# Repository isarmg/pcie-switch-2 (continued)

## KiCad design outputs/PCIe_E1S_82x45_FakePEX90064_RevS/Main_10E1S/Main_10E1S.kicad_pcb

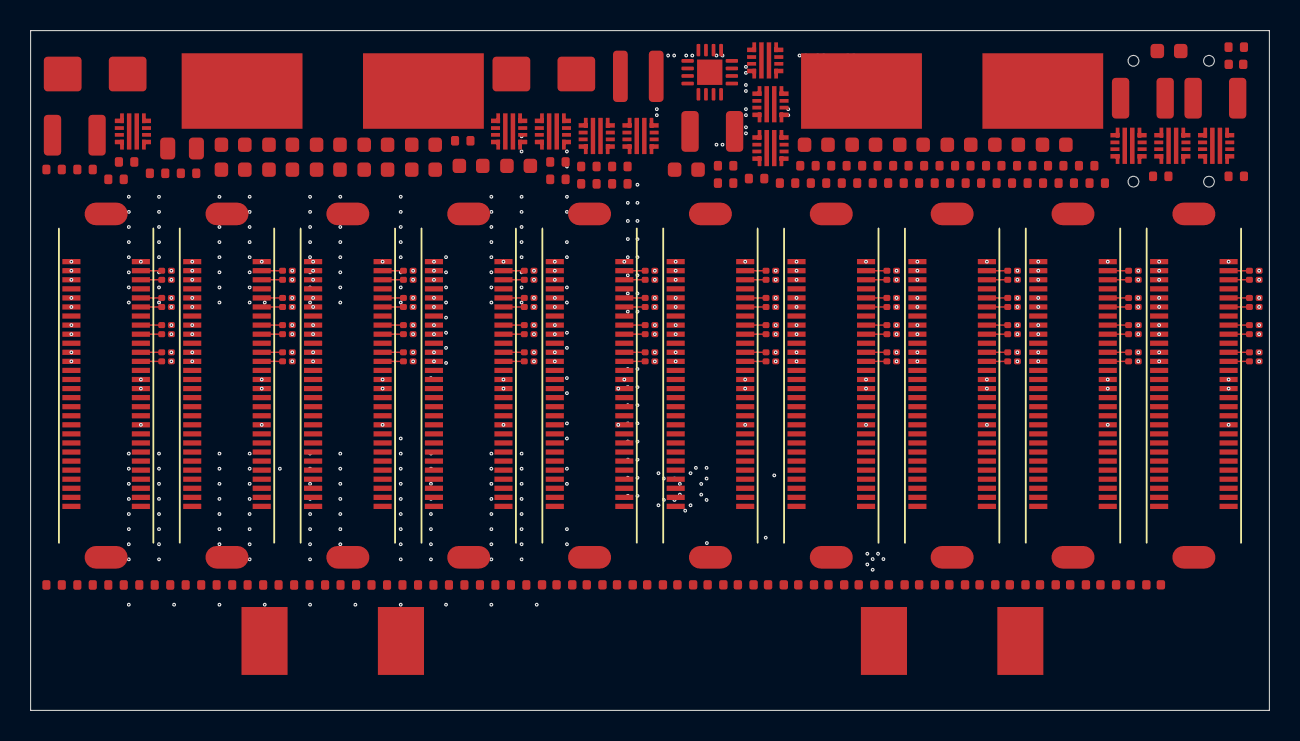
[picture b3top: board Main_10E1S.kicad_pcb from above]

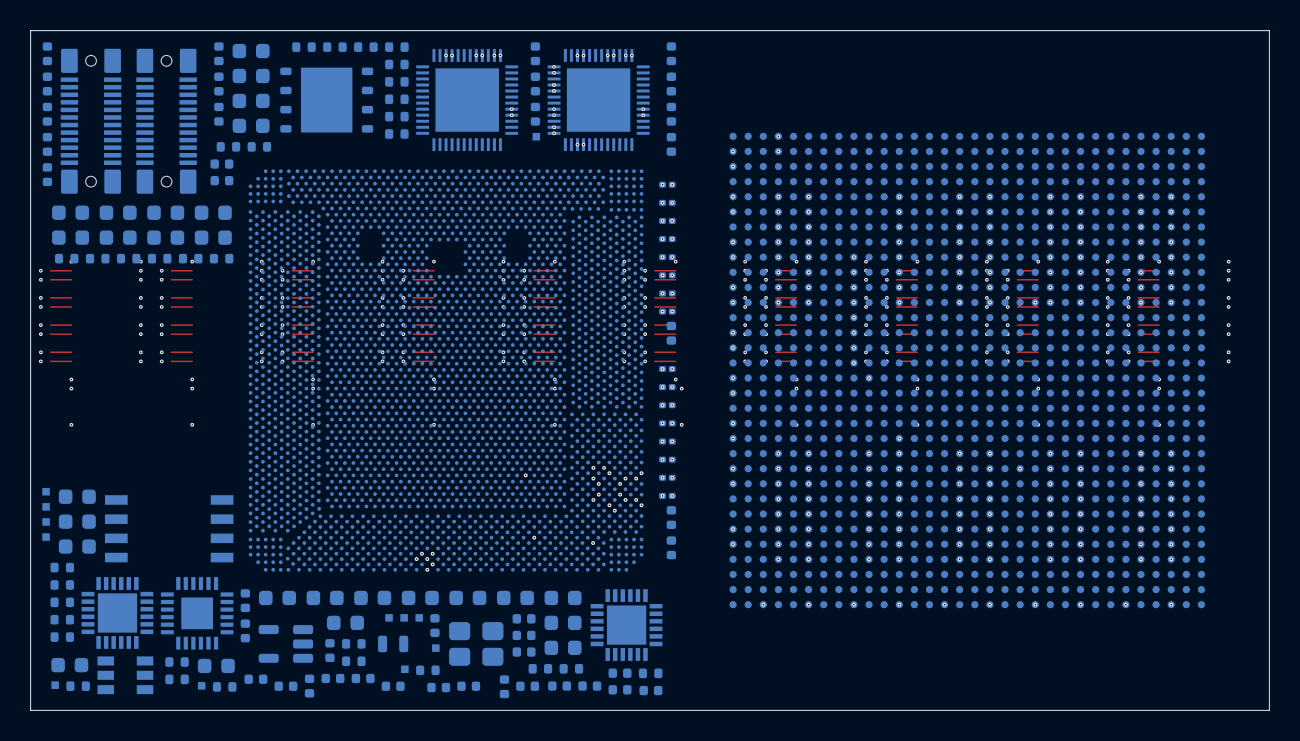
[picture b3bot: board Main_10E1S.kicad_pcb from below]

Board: 32 copper layers, 82.0 x 45.0 mm, 357 parts (145 on the bottom side), 466 nets.

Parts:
C1, C2: 10uF 25V X7R; C_1210_3225Metric
C101, C104, C107, C110, C113, C116, C119, C122, C125, C128, C301: 10nF 25V; C_0402_1005Metric
C102, C105, C108, C111, C114, C117, C120, C123, C126, C129: 100nF 50V; C_0603_1608Metric
C103, C106, C109, C112, C115, C118, C121, C124, C127, C130: 1uF 25V; C_0603_1608Metric
C311: 10uF 25V; C_0805_2012Metric
C312: 100nF 50V; C_0402_1005Metric
C313: 3.3nF 25V; C_0402_1005Metric
C314, C315: 47uF 16V; C_1210_3225Metric
C701, C720, C721, C722, C723, C724, C725, C726, C727, C728, C730, C731, C732, C733, C734, C735, C736, C737, C738, C742: 100nF; C_0402_1005Metric
C702, C707, C708: 1uF; C_0402_1005Metric
C703, C704: 18pF DNP TUNE; C_0402_1005Metric
C705, C706: 8.2pF DNP TUNE; C_0402_1005Metric
C709, C710: 100nF RC reset draft; C_0402_1005Metric
C741: 47nF / reset delay; C_0402_1005Metric
C801, C802, C803, C804, C805, C806, C807, C808, C811, C812, C813, C814, C815, C816, C817, C818: 220nF 16V / GRM033R61C224KE14D; C_0201_0603Metric
C901, C903, C905, C907, C909, C911, C913, C915, C917, C919, C921, C923, C925, C927, C929, C931, C933: 100nF / PDN budget; C_0402_1005Metric
C902, C904, C906, C908, C910, C912, C914, C916, C918, C920, C922, C924, C926, C928, C930, C932, C934: 4.7uF / PDN budget; C_0603_1608Metric
C951, C952, C953, C954, C955, C956, C957, C958, C959, C960: 4.7uF / EDGECAP value pending PDG; C_0603_1608Metric
C965, C966, C967, C968: 1uF / filter value pending PDG; C_0402_1005Metric
C4001, C4002, C4003, C4004, C4005, C4006, C4007, C4008, C4009, C4010, C4011, C4012, C4013, C4014, C4015, C4016, C4017, C4018, C4019, C4020, C4021, C4022, C4023, C4024, C4025, C4026, C4027, C4028, C4029, C4030, C4031, C4032, C4033, C4034, C4035, C4036, C4037, C4038, C4039, C4040, C4041, C4042, C4043, C4044, C4045, C4046, C4047, C4048, C4049, C4050, C4051, C4052, C4053, C4054, C4055, C4056, C4057, C4058, C4059, C4060, C4061, C4062, C4063, C4064, C4065, C4066, C4067, C4068, C4069, C4070, C4071, C4072, C4073, C4074, C4075, C4076, C4077, C4078, C4079, C4080: 220nF 16V / GRM033R61C224KE14D; C_0201_0603Metric_DenseCourtyard_1p30x0p55
D1, D2: SMBJ13CA; D_SMB
F1, F2: 20A 125V; Littelfuse_456_20A
J1, J2, J3, J4, J5, J6, J7, J8, J9, J10: HSEC6-028-01-S-DV-WT-TR; Samtec_HSEC6-028-01-S-DV-WT
J11: 12V 15A FEED A; WireSolder_2x_8x5_P12
J12: 12V 15A FEED B; WireSolder_2x_8x5_P12
J401: CUSTOM 12V POWER / SMT SHELL DRAFT; USB_C_24P_Vertical_SMT_Shell_7p46_CUSTOM_DRAFT
J402: TB5 PORT / SMT SHELL DRAFT / PART TBD; USB_C_24P_Vertical_SMT_Shell_7p46_CUSTOM_DRAFT
L31: 2.2uH; L_Coilcraft_XAL4020-XXX
R101, R106, R111, R116, R121, R126, R131, R136, R141, R146, R301: 76.1k; R_0402_1005Metric
R102, R104, R107, R109, R112, R114, R117, R119, R122, R124, R127, R129, R132, R134, R137, R139, R142, R144, R147, R149, R302, R304, R702, R703, R704, R712, R713, R724, R725: 10k; R_0402_1005Metric
R103, R108, R113, R118, R123, R128, R133, R138, R143, R148, R303: 102k; R_0402_1005Metric
R105, R110, R115, R120, R125, R130, R135, R140, R145, R150: 1.10k; R_0402_1005Metric
R305: 3.32k; R_0402_1005Metric
R311, R401, R402, R710, R711: 100k; R_0402_1005Metric
R701: 22R provisional SI tuning; R_0402_1005Metric
R705: 180R 1% / Intel clock topology; R_0402_1005Metric
R706, R707: TBD RCOMP / DNP / Intel PDG required; R_0402_1005Metric
R708, R709: 200R 1%; R_0402_1005Metric
R714, R715, R716: 0R / request clock always on; R_0402_1005Metric
R721, R722: 0R analog supply link / filter pending; R_0402_1005Metric
R730, R731, R732: DNP / filter link pending Intel PDG; R_0402_1005Metric
R740, R741, R742, R743, R744, R745, R746: 10k / Intel required external bias; R_0402_1005Metric
TP701: PROBE /CPU_SVID_CLK_1V25; Probe_0p5mm
TP702: PROBE /CPU_SVID_DATA_1V25; Probe_0p5mm
TP703: PROBE /CPU_SVID_ALERT_1V25_N; Probe_0p5mm
TP704: PROBE /CPU_PLT_PWROK; Probe_0p5mm
TP705: PROBE /CPU_SYS_PWROK_1V8; Probe_0p5mm
TP706: PROBE /CPU_RSMRST_N; Probe_0p5mm
TP707: PROBE /CPU_SYS_RESET_1V8_N; Probe_0p5mm
TP708: PROBE /CPU_PWRBTN_1V8_N; Probe_0p5mm
TP709: PROBE /CPU_VCCST_EN_1V8; Probe_0p5mm
TP710: PROBE /CPU_SLP_S3_1V8_N; Probe_0p5mm
TP711: PROBE /CPU_SLP_S4_1V8_N; Probe_0p5mm
TP712: PROBE /CPU_SLP_S5_1V8_N; Probe_0p5mm
U1: PEX90064 / FAKE 64-lane 33x33 BGA1024; PEX90064_FAKE_BGA1024_33x33_P1_Reordered_NOT_REAL
U11, U12, U13, U14, U15, U16, U17, U18, U19, U20, U30: TPS259470ARPWR; TI_RPW0010A_TPS25947
U31: TPS62132RGTR; VQFN-16-1EP_3x3mm_P0.5mm_EP1.68x1.68mm
U501: Intel_JHL9580_MECH_13x13_UNVERIFIED
U502: Intel Core Ultra 9 288V / 32GB LPDDR5X MoP / BGA2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; Intel_Core_Ultra_200V_BGA2833_27p5x27_ExactXY_DraftLands
U601: 9ZXL0851EKILFT / CPU common clock 100MHz; REF_9ZXL0851EKILFT_KU1
U602: 9ZXL0851EKILFT / CPU common clock 100MHz; REF_9ZXL0851EKILFT_KU3
U603: 9FGV0241AKLF / DNP ALTERNATE CLOCK; REF_9FGV0241AKLF_KU2
U604: 9DML0451AKILF / DNP ALTERNATE CLOCK; REF_9DML0451AKILF_KU5
U605: TPS3808G09DBVR / SUPPORT NETWORK PENDING; REF_TPS3808G09DBVR_FU1
U606: W25Q32JWSSIQ_C2980995 / SUPPORT NETWORK PENDING; REF_W25Q32JWSSIQ_FU2
U607: TCA9548ARGER / SUPPORT NETWORK PENDING; REF_TCA9548ARGER_SU1
U701: W25Q256JWPIQ / 1.8V 32MiB BIOS; WSON-8-1EP_6x5mm_P1.27mm_EP3.4x4.3mm
U702: TPS7A0215PDBVR / RTC 1.5V; SOT-23-5
Y701: 38.4MHz crystal / load and ESR selection pending; Crystal_SMD_3225-4Pin_3.2x2.5mm
Y702: 32.768kHz crystal / load and ESR selection pending; Crystal_SMD_2012-2Pin_2.0x1.2mm

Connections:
/AUX_12V_PROTECTED: C311.1, C312.1, U30.6, U31.10, U31.11, U31.12, U31.13
/AUX_DVDT: C301.1, U30.7
/AUX_ILM: R305.1, U30.9
/AUX_OV: R303.2, R304.1, U30.2
/AUX_PG: R311.2, U31.4
/AUX_UV: R301.2, R302.1, U30.1
/BUCK_SS: C313.1, U31.9
/BUCK_SW: L31.1, U31.1, U31.2, U31.3
/CLKBUF1_VDDA: C728.1, R721.2, U601.44
/CLKBUF2_VDDA: C738.1, R722.2, U602.44
/CPU_ACPRESENT: R741.1, U502.P45
/CPU_BATLOW_N: R740.1, U502.R50
/CPU_CLKBUF1_IN_N: U502.BC2, U601.5
/CPU_CLKBUF1_IN_P: U502.BB1, U601.4
/CPU_CLKBUF2_IN_N: U502.AY4, U602.5
/CPU_CLKBUF2_IN_P: U502.AW3, U602.4
/CPU_CLKREQ0_N: R714.1, U502.B55
/CPU_CLKREQ1_N: R715.1, U502.F50
/CPU_CLKREQ2_N: R716.1, U502.E51
/CPU_CLK_RCOMP: R705.1, U502.BG3
/CPU_EPD_ON_LOOP_1V25: U502.AB27, U502.Y27
/CPU_G5_RX0_N: C812.2, U502.DD16
/CPU_G5_RX0_P: C811.2, U502.DE14
/CPU_G5_RX1_N: C814.2, U502.DA18
/CPU_G5_RX1_P: C813.2, U502.CY17
/CPU_G5_RX2_N: C816.2, U502.CY22
/CPU_G5_RX2_P: C815.2, U502.DA21
/CPU_G5_RX3_N: C818.2, U502.DC24
/CPU_G5_RX3_P: C817.2, U502.DD23
/CPU_G5_TX0_N: C802.1, U502.DL16
/CPU_G5_TX0_P: C801.1, U502.DK17
/CPU_G5_TX1_N: C804.1, U502.DH17
/CPU_G5_TX1_P: C803.1, U502.DF18
/CPU_G5_TX2_N: C806.1, U502.DH22
/CPU_G5_TX2_P: C805.1, U502.DF21
/CPU_G5_TX3_N: C808.1, U502.DL23
/CPU_G5_TX3_P: C807.1, U502.DK22
/CPU_PCIE4_RCOMP: R706.1, U502.DL39
/CPU_PCIE5_RCOMP: R707.1, U502.DA1
/CPU_PERST_1V8_N: R725.1, U1.AM32, U502.F24, U605.3
/CPU_PEX_RX0_N: C802.2, U1.AD32
/CPU_PEX_RX0_P: C801.2, U1.AC32
/CPU_PEX_RX1_N: C804.2, U1.AA32
/CPU_PEX_RX1_P: C803.2, U1.Y32
/CPU_PEX_RX2_N: C806.2, U1.V32
/CPU_PEX_RX2_P: C805.2, U1.U32
/CPU_PEX_RX3_N: C808.2, U1.R32
/CPU_PEX_RX3_P: C807.2, U1.P32
/CPU_PEX_TX0_N: C812.1, U1.M32
/CPU_PEX_TX0_P: C811.1, U1.L32
/CPU_PEX_TX1_N: C814.1, U1.J32
/CPU_PEX_TX1_P: C813.1, U1.H32
/CPU_PEX_TX2_N: C816.1, U1.F32
/CPU_PEX_TX2_P: C815.1, U1.E32
/CPU_PEX_TX3_N: C818.1, U1.C32
/CPU_PEX_TX3_P: C817.1, U1.B32
/CPU_PLT_PWROK: R745.1, TP704.1, U502.H13
/CPU_PMCALERT_N: R742.1, U502.F42
/CPU_PWRBTN_1V8_N: R713.1, TP708.1, U502.P47
/CPU_REFCLK_N: U1.AH32, U502.BC4
/CPU_REFCLK_P: U1.AG32, U502.BB3
/CPU_RSMRST_N: R744.1, TP706.1, U502.E13
/CPU_RTCRST_N: C709.1, R710.1, U502.H15
/CPU_RTCX1: C705.1, U502.A12, Y702.1
/CPU_RTCX2: C706.1, U502.A10, Y702.2
/CPU_SLP_S3_1V8_N: TP710.1, U502.M44
/CPU_SLP_S4_1V8_N: TP711.1, U502.L55
/CPU_SLP_S5_1V8_N: TP712.1, U502.P53
/CPU_SPI_CLK_FLASH: R701.2, U701.6
/CPU_SPI_CLK_PAD: R701.1, U502.W13
/CPU_SPI_CS0_N: R702.1, U502.AC17, U701.1
/CPU_SPI_IO0: U502.AA17, U701.5
/CPU_SPI_IO1: U502.AE17, U701.2
/CPU_SPI_IO2: R703.1, U502.W17, U701.3
/CPU_SPI_IO3: R704.1, U502.U13, U701.7
/CPU_SRTCRST_N: C710.1, R711.1, U502.B15
/CPU_SVID_ALERT_1V25_N: TP703.1, U502.F56
/CPU_SVID_CLK_1V25: TP701.1, U502.E55
/CPU_SVID_DATA_1V25: TP702.1, U502.C56
/CPU_SYS_PWROK_1V8: R746.1, TP705.1, U502.H31
/CPU_SYS_RESET_1V8_N: R712.1, TP707.1, U502.M52
/CPU_USB2_RCOMP: R708.1, U502.W1
/CPU_USB32_RCOMP: R709.1, U502.BG1
/CPU_V1P8U_MEM: C901.1, C902.1, U502.AK67, U502.AK70, U502.AL69, U502.AM67, U502.AM70, U502.AP67, U502.AP70, U502.AR69, U502.AT67, U502.AT70, U502.AT73, U502.AT76, U502.AT79, U502.AU69, U502.AU75, U502.AU80, U502.AV67, U502.AV70, U502.AV73, U502.AV76, U502.AV79, U502.AW69, U502.AW72, U502.AW75, U502.AW77, U502.AW80, U502.AY67, U502.AY70, U502.AY73, U502.AY76, U502.AY79, U502.BA72, U502.BA77, U502.BB67, U502.BB70, U502.BB73, U502.BB76, U502.BB79, U502.BC69, U502.BC77, U502.BC80, U502.BD67, U502.BD79, U502.BD82, U502.BD85, U502.BD88, U502.BD90, U502.BD93, U502.BE69, U502.BE80, U502.BE86, U502.BF67, U502.BF79, U502.BF82, U502.BF85, U502.BF88, U502.BF90, U502.BF93, U502.BG69, U502.BG77, U502.BG80, U502.BG83, U502.BG86, U502.BG89, U502.BG92, U502.BH67, U502.BH79, U502.BH82, U502.BH85, U502.BH88, U502.BH90, U502.BH93, U502.BJ77, U502.BK67, U502.BK79, U502.BL69, U502.BL72, U502.BL77, U502.BL80, U502.BM67, U502.BM70, U502.BM73, U502.BM76, U502.BM79, U502.BN69, U502.BN75, U502.BN80, U502.BP67, U502.BP70, U502.BP73, U502.BP76, U502.BP79, U502.BR69, U502.BR72, U502.BR75, U502.BR77, U502.BR80, U502.BT67, U502.BT70, U502.BT73, U502.BT76, U502.BT79, U502.BV67, U502.BV70, U502.BW69, U502.BY67, U502.BY70, U502.CA69, U502.CB67, U502.CB70
/CPU_V1P8U_MEM_EDGECAP_0: C951.1, U502.B69, U502.B71
/CPU_V1P8U_MEM_EDGECAP_1: C952.1, U502.AE92, U502.AG92
/CPU_V1P8U_MEM_EDGECAP_2: C953.1, U502.CE92, U502.CG92
/CPU_V1P8U_MEM_EDGECAP_3: C954.1, U502.DK68, U502.DK70
/CPU_VCCGT: C903.1, C904.1, U502.A34, U502.A36, U502.A38, U502.A40, U502.A42, U502.A44, U502.A46, U502.A48, U502.A50, U502.A52, U502.A54, U502.A56, U502.A58, U502.A60, U502.A88, U502.A90, U502.AA34, U502.AA40, U502.AA46, U502.AA51, U502.AA57, U502.AA63, U502.AA69, U502.AA75, U502.AA80, U502.AA86, U502.AB30, U502.AB33, U502.AB36, U502.AB38, U502.AB41, U502.AB44, U502.AB47, U502.AB50, U502.AB53, U502.AB56, U502.AB59, U502.AB62, U502.AB64, U502.AB67, U502.AB70, U502.AB73, U502.AB76, U502.AB79, U502.AB82, U502.AB85, U502.AB88, U502.AB90, U502.AB93, U502.AC31, U502.AC34, U502.AC37, U502.AC40, U502.AC43, U502.AC46, U502.AC49, U502.AC51, U502.AC54, U502.AC57, U502.AC60, U502.AC63, U502.AC66, U502.AC69, U502.AC72, U502.AC75, U502.AC77, U502.AC80, U502.AC83, U502.AC86, U502.AC89, U502.AC92, U502.AD30, U502.AD33, U502.AD36, U502.AD38, U502.AD41, U502.AD44, U502.AD47, U502.AD50, U502.AD53, U502.AD56, U502.AD59, U502.AD62, U502.AD64, U502.AD67, U502.AD70, U502.AD73, U502.AD76, U502.AD79, U502.AD82, U502.AD85, U502.AD88, U502.AD90, U502.AD93, U502.AE31, U502.AE37, U502.AE43, U502.AE49, U502.AE54, U502.AE60, U502.AE66, U502.AE72, U502.AE77, U502.AE83, U502.AE89, U502.AF30, U502.AF33, U502.AF36, U502.AF38, U502.AF41, U502.AF44, U502.AF47, U502.AF50, U502.AF53, U502.AF56, U502.AF59, U502.AF62, U502.AF64, U502.AF67, U502.AF70, U502.AF73, U502.AF76, U502.AF79, U502.AF82, U502.AF85, U502.AF88, U502.AG31, U502.AG34, U502.AG37, U502.AG40, U502.AG43, U502.AG46, U502.AG49, U502.AG51, U502.AG54, U502.AG57, U502.AG60, U502.AG63, U502.AG66, U502.AG69, U502.AG72, U502.AG80, U502.AG83, U502.AG86, U502.AG89, U502.AH30, U502.AH33, U502.AH36, U502.AH38, U502.AH41, U502.AH44, U502.AH47, U502.AH50, U502.AH53, U502.AH56, U502.AH59, U502.AH62, U502.AH64, U502.AH67, U502.AH70, U502.AH82, U502.AH85, U502.AH88, U502.AJ34, U502.AJ40, U502.AJ46, U502.AJ51, U502.AJ57, U502.AJ63, U502.AJ69, U502.AJ80, U502.AJ86, U502.AK30, U502.AK33, U502.AK36, U502.AK38, U502.AK41, U502.AK44, U502.AK47, U502.AK50, U502.AK53, U502.AK56, U502.AK59, U502.AK62, U502.AK64, U502.AK82, U502.AK85, U502.AK88, U502.AL31, U502.AL34, U502.AL37, U502.AL40, U502.AL43, U502.AL46, U502.AL49, U502.AL51, U502.AL54, U502.AL57, U502.AL60, U502.AL63, U502.AL66, U502.AM30, U502.AM33, U502.AM36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
/CPU_VCCL2: C905.1, C906.1, U502.BV41, U502.BV44, U502.BV47, U502.BW40, U502.BW43, U502.BW46
/CPU_VCCPRIM_1P8: C701.1, C702.1, C907.1, C908.1, R702.2, R703.2, R704.2, R712.2, R713.2, R725.2, R730.1, R731.1, R740.2, R741.2, R742.2, R743.2, U502.AR20, U502.AR23, U502.AR26, U502.AT21, U502.AT24, U502.AU20, U502.AU23, U502.AU26, U701.8
/CPU_VCCPRIM_1P8_FLTRA_IN: C966.1, R730.2, U502.BJ20, U502.BL20, U502.BN20
/CPU_VCCPRIM_1P8_FLTRB_CAP: C965.1, U502.CN31, U502.CN34, U502.CP30, U502.CP33
/CPU_VCCPRIM_1P8_FLTRB_IN: C967.1, R731.2, U502.AR17, U502.AT18, U502.AU17
/CPU_VCCPRIM_3P3: C909.1, C910.1, U502.AW17, U502.BA17
/CPU_VCCPRIM_IO: C911.1, C912.1, U502.BB18, U502.BC17, U502.BD18, U502.BE17, U502.BF18, U502.BG17, U502.BH18, U502.BJ17, U502.BK18, U502.BL17, U502.BM18, U502.BN17, U502.BP18, U502.BR17, U502.BT18, U502.BU17, U502.BV18, U502.BW17, U502.BY18, U502.CA17, U502.CB18, U502.CC17, U502.CD18, U502.CE17, U502.CF18, U502.CG17, U502.CH18, U502.CJ17, U502.CK18, U502.CL17, U502.CM18, U502.CN17, U502.CN20, U502.CN23, U502.CN26, U502.CN28, U502.CP18, U502.CP21, U502.CP24, U502.CP27
/CPU_VCCPRIM_VNNAON: C913.1, C914.1, R732.1, U502.AW20, U502.AW23, U502.AW26, U502.AY21, U502.AY24, U502.AY27, U502.BA20, U502.BA26, U502.BB21, U502.BB24, U502.BB27, U502.BC20, U502.BC23, U502.BC26, U502.BD21, U502.BD24, U502.BD27, U502.BE23, U502.BF24, U502.BF27, U502.BG23, U502.BG26, U502.BH21, U502.BH24, U502.BJ23, U502.BJ26, U502.BK24, U502.BL23, U502.BL26, U502.BM24, U502.BN23, U502.BP21, U502.BP24, U502.BR20, U502.BR23, U502.BT21, U502.BT24, U502.BU20, U502.BV21, U502.BV24, U502.BW20, U502.BW23, U502.BY21, U502.BY24, U502.CA23, U502.CB21, U502.CB24, U502.CC20, U502.CC23, U502.CD21, U502.CD24, U502.CE20, U502.CF21, U502.CG20, U502.CG23, U502.CH21, U502.CJ23, U502.CK21, U502.CK24, U502.CK27, U502.CK30, U502.CL20, U502.CL23, U502.CL26, U502.CL28
/CPU_VCCPRIM_VNNAONLV: C915.1, C916.1, U502.BK27, U502.BK30, U502.BL28, U502.BM27, U502.BM30, U502.BN28, U502.BP27, U502.BP30, U502.BR26, U502.BR28, U502.BT27, U502.BT30, U502.BU26, U502.BV27, U502.BV30, U502.BW26, U502.BW28, U502.BY27, U502.BY30, U502.CA28, U502.CB27, U502.CB30, U502.CC26, U502.CC28, U502.CD27, U502.CD30, U502.CE26, U502.CF24, U502.CF27, U502.CF30, U502.CG26, U502.CG28, U502.CH24, U502.CH27, U502.CH30, U502.CJ28
/CPU_VCCPRIM_VNNAON_FLTR: C968.1, R732.2, U502.BE20, U502.BG20
/CPU_VCCRTC: C708.1, C917.1, C918.1, R710.2, R711.2, U502.AN20, U702.5
/CPU_VCCSA: C919.1, C920.1, U502.AU34, U502.AU40, U502.AU46, U502.AU51, U502.AV33, U502.AV36, U502.AV38, U502.AV41, U502.AV44, U502.AV47, U502.AV50, U502.AV53, U502.AV56, U502.AW34, U502.AW37, U502.AW40, U502.AW43, U502.AW46, U502.AW49, U502.AW51, U502.AW54, U502.AY33, U502.AY36, U502.AY38, U502.AY41, U502.AY44, U502.AY47, U502.AY50, U502.AY53, U502.AY56, U502.BA31, U502.BA37, U502.BA43, U502.BA49, U502.BA54, U502.BB33, U502.BB36, U502.BB38, U502.BB41, U502.BB44, U502.BB47, U502.BB50, U502.BB53, U502.BB56, U502.BC31, U502.BC34, U502.BC40, U502.BC43, U502.BC46, U502.BC49, U502.BC51, U502.BC54, U502.BD33, U502.BD36, U502.BD38, U502.BD41, U502.BD44, U502.BD47, U502.BD50, U502.BD53, U502.BD56, U502.BE31, U502.BE34, U502.BE37, U502.BE40, U502.BE46, U502.BE51, U502.BF33, U502.BF36, U502.BF38, U502.BF41, U502.BF44, U502.BF47, U502.BF50, U502.BF53, U502.BF56, U502.BG31, U502.BG34, U502.BG37, U502.BG40, U502.BG43, U502.BG46, U502.BG49, U502.BG51, U502.BG54, U502.BH33, U502.BH36, U502.BH38, U502.BH41, U502.BH44, U502.BH47, U502.BH50, U502.BH53, U502.BH56, U502.BJ31, U502.BJ37, U502.BJ54, U502.BK33, U502.BK36, U502.BK50, U502.BK53, U502.BK56, U502.BL31, U502.BL34, U502.BL37, U502.BL49, U502.BL51, U502.BL54, U502.BM33, U502.BM36, U502.BM50, U502.BM53, U502.BM56, U502.BN37, U502.BN51, U502.BP33, U502.BP36, U502.BP50, U502.BP53, U502.BP56, U502.BR31, U502.BR34, U502.BR37, U502.BR49, U502.BR51, U502.BR54, U502.BT33, U502.BT36, U502.BT50, U502.BT53, U502.BT56, U502.BU31, U502.BU37, U502.BU49, U502.BU54, U502.BV33, U502.BV36, U502.BV50, U502.BV53, U502.BV56, U502.BW31, U502.BW34, U502.BW37, U502.BW49, U502.BW51, U502.BW54, U502.BY33, U502.CA34, U502.CB33, U502.CC31, U502.CC34, U502.CD33, U502.CE31, U502.CE34, U502.CF33, U502.CG31, U502.CG34, U502.CH33, U502.CJ34, U502.CK33, U502.CL31, U502.CL34
/CPU_VCCST: C921.1, C922.1, U502.AU31, U502.AV30
/CPU_VCCST_EN_1V8: TP709.1, U502.M48
/CPU_VCC_ECORE: C923.1, C924.1, U502.BJ40, U502.BJ43, U502.BJ46, U502.BK38, U502.BK41, U502.BK44, U502.BK47, U502.BL43, U502.BM38, U502.BM41, U502.BM44, U502.BM47, U502.BN40, U502.BN43, U502.BN46, U502.BP38, U502.BP41, U502.BP44, U502.BP47, U502.BR43, U502.BT38, U502.BT41, U502.BT44, U502.BT47, U502.BU40, U502.BU43, U502.BU46, U502.BV38
/CPU_VCC_PCORE: C925.1, C926.1, U502.CA40, U502.CA46, U502.CA51, U502.CA57, U502.CA63, U502.CB36, U502.CB38, U502.CB41, U502.CB44, U502.CB47, U502.CB50, U502.CB53, U502.CB56, U502.CB59, U502.CB62, U502.CB64, U502.CC37, U502.CC40, U502.CC43, U502.CC46, U502.CC49, U502.CC51, U502.CC54, U502.CC57, U502.CC60, U502.CC63, U502.CC66, U502.CC69, U502.CC72, U502.CC80, U502.CC83, U502.CC86, U502.CD36, U502.CD38, U502.CD41, U502.CD44, U502.CD47, U502.CD50, U502.CD53, U502.CD56, U502.CD59, U502.CD62, U502.CD64, U502.CD67, U502.CD70, U502.CD82, U502.CD85, U502.CD88, U502.CE37, U502.CE43, U502.CE49, U502.CE54, U502.CE60, U502.CE66, U502.CE72, U502.CE83, U502.CE89, U502.CF36, U502.CF38, U502.CF41, U502.CF44, U502.CF47, U502.CF50, U502.CF53, U502.CF56, U502.CF59, U502.CF62, U502.CF64, U502.CF67, U502.CF70, U502.CF73, U502.CF76, U502.CF79, U502.CF82, U502.CF85, U502.CF88, U502.CG37, U502.CG40, U502.CG43, U502.CG46, U502.CG49, U502.CG51, U502.CG54, U502.CG57, U502.CG60, U502.CG63, U502.CG66, U502.CG69, U502.CG72, U502.CG77, U502.CG80, U502.CG83, U502.CG86, U502.CG89, U502.CH36, U502.CH38, U502.CH41, U502.CH44, U502.CH47, U502.CH50, U502.CH53, U502.CH56, U502.CH59, U502.CH62, U502.CH64, U502.CH67, U502.CH70, U502.CH73, U502.CH76, U502.CH79, U502.CH82, U502.CH85, U502.CH88, U502.CH90, U502.CH93, U502.CJ40, U502.CJ46, U502.CJ51, U502.CJ57, U502.CJ63, U502.CJ69, U502.CJ75, U502.CJ80, U502.CJ86, U502.CJ92, U502.CK36, U502.CK38, U502.CK41, U502.CK44, U502.CK47, U502.CK50, U502.CK53, U502.CK56, U502.CK59, U502.CK62, U502.CK64, U502.CK67, U502.CK70, U502.CK73, U502.CK76, U502.CK79, U502.CK82, U502.CK85, U502.CK88, U502.CK90, U502.CK93, U502.CL37, U502.CL40, U502.CL43, U502.CL46, U502.CL49, U502.CL51, U502.CL54, U502.CL57, U502.CL60, U502.CL63, U502.CL66, U502.CL69, U502.CL72, U502.CL75, U502.CL77, U502.CL80, U502.CL83, U502.CL86, U502.CL89, U502.CM36, U502.CM38, U502.CM41, U502.CM44, U502.CM47, U502.CM50, U502.CM53, U502.CM56, U502.CM59, U502.CM62, U502.CM64, U502.CM67, U502.CM70, U502.CM73, U502.CM76, U502.CM79, U502.CM82, U502.CM85, U502.CM88, U502.CM90, U502.CM93, U502.CN37, U502.CN43, U502.CN49, U502.CN54, U502.CN60, U502.CN66, U502.CN72, U502.CN77, U502.CN83, U502.CN89, U502.CN92, U502.CP36, U502.CP38, U502.CP41, U502.CP44, U502.CP47, U502.CP50, U502.CP53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
/CPU_VDD2H: C927.1, C928.1, U502.BJ83, U502.BJ89, U502.BK82, U502.BK85, U502.BK88, U502.BK90, U502.BK93, U502.BL83, U502.BL86, U502.BL89, U502.BL92, U502.BM82, U502.BM85, U502.BM88, U502.BM90, U502.BM93, U502.BN86, U502.BP82, U502.BP85, U502.BP88, U502.BP90, U502.BP93, U502.BR83, U502.BR86, U502.BR89, U502.BR92, U502.BT82, U502.BT85, U502.BT88, U502.BT90, U502.BT93
/CPU_VDD2H_EDGECAP_0: C955.1, U502.B81, U502.B83, U502.B86
/CPU_VDD2H_EDGECAP_1: C956.1, U502.DK80, U502.DK82, U502.DK84
/CPU_VDD2L: C929.1, C930.1, U502.AL72, U502.AL80, U502.AL83, U502.AL86, U502.AL89, U502.AL92, U502.AM73, U502.AM76, U502.AM79, U502.AM82, U502.AM85, U502.AM88, U502.AN72, U502.AN77, U502.AN83, U502.AN89, U502.AN92, U502.AP73, U502.AP76, U502.AP79, U502.AP82, U502.AP85, U502.AP88, U502.AR72, U502.AR75, U502.AR77, U502.AR80, U502.AR83, U502.AR86, U502.AR89, U502.AR92, U502.BU72, U502.BU77, U502.BU83, U502.BU89, U502.BU92, U502.BV73, U502.BV76, U502.BV79, U502.BV82, U502.BV85, U502.BV88, U502.BW72, U502.BW75, U502.BW77, U502.BW80, U502.BW83, U502.BW86, U502.BW89, U502.BW92, U502.BY73, U502.BY76, U502.BY79, U502.BY82, U502.BY85, U502.BY88, U502.CA80, U502.CA86, U502.CA89, U502.CA92, U502.CB82, U502.CB85, U502.CB88
/CPU_VDD2L_EDGECAP_0: C957.1, U502.B73
/CPU_VDD2L_EDGECAP_1: C958.1, U502.DK72
/CPU_VDD2_PWRGOOD_LOOP: U502.AA26, U502.AC26
/CPU_VDDQ: C931.1, C932.1, U502.AT82, U502.AT85, U502.AT88, U502.AT90, U502.AT93, U502.AU86, U502.AV82, U502.AV85, U502.AV88, U502.AV90, U502.AV93, U502.AW83, U502.AW86, U502.AW89, U502.AW92, U502.AY82, U502.AY85, U502.AY88, U502.AY90, U502.AY93, U502.BA83, U502.BA89, U502.BB82, U502.BB85, U502.BB88, U502.BB90, U502.BB93, U502.BC83, U502.BC86, U502.BC89, U502.BC92
/CPU_VDDQ_EDGECAP_0: C959.1, U502.B75, U502.B77, U502.B79
/CPU_VDDQ_EDGECAP_1: C960.1, U502.DK74, U502.DK76, U502.DK78
/CPU_VDDRIO: C933.1, C934.1, U502.AR57, U502.AR60, U502.AR63, U502.AR66, U502.AT59, U502.AT62, U502.AT64, U502.AU57, U502.AU63, U502.AV59, U502.AV62, U502.AV64, U502.AW57, U502.AW60, U502.AW63, U502.AW66, U502.AY59, U502.AY62, U502.AY64, U502.BA60, U502.BA66, U502.BB59, U502.BB62, U502.BB64, U502.BC57, U502.BC60, U502.BC63, U502.BC66, U502.BD59, U502.BD62, U502.BD64, U502.BE57, U502.BE63, U502.BF59, U502.BF62, U502.BF64, U502.BG57, U502.BG60, U502.BG63, U502.BG66, U502.BH59, U502.BH62, U502.BH64, U502.BJ60, U502.BJ66, U502.BK59, U502.BK62, U502.BK64, U502.BL57, U502.BL60, U502.BL63, U502.BM59, U502.BM62, U502.BM64, U502.BN57, U502.BN63, U502.BP59, U502.BP62, U502.BP64, U502.BR57, U502.BR60, U502.BR63, U502.BT59, U502.BT62, U502.BT64, U502.BU60, U502.BU66, U502.BV59, U502.BV62, U502.BV64, U502.BW57, U502.BW60, U502.BW63, U502.BW66, U502.BY59, U502.BY62, U502.BY64
/CPU_WAKE_N: R743.1, U502.P49
/CPU_XTAL_IN: C703.1, U502.M1, Y701.1
/CPU_XTAL_OUT: C704.1, U502.N2, Y701.3
/CUSTOM_12V_RAW: J401.A4, J401.A6, J401.A7, J401.A8, J401.A9, J401.B4, J401.B6, J401.B7, J401.B8, J401.B9
/CUSTOM_DET_A: J401.A5, R401.1
/CUSTOM_DET_B: J401.B5, R402.1
/GND: C1.2, C2.2, C101.2, C102.2, C103.2, C104.2, C105.2, C106.2, C107.2, C108.2, C109.2, C110.2, C111.2, C112.2, C113.2, C114.2, C115.2, C116.2, C117.2, C118.2, C119.2, C120.2, C121.2, C122.2, C123.2, C124.2, C125.2, C126.2, C127.2, C128.2, C129.2, C130.2, C301.2, C311.2, C312.2, C313.2, C314.2, C315.2, C701.2, C702.2, C703.2, C704.2, C705.2, C706.2, C707.2, C708.2, C709.2, C710.2, C720.2, C721.2, C722.2, C723.2, C724.2, C725.2, C726.2, C727.2, C728.2, C730.2, C731.2, C732.2, C733.2, C734.2, C735.2, C736.2, C737.2, C738.2, C741.2, C742.2, C901.2, C902.2, C903.2, C904.2, C905.2, C906.2, C907.2, C908.2, C909.2, C910.2, C911.2, C912.2, C913.2, C914.2, C915.2, C916.2, C917.2, C918.2, C919.2, C920.2, C921.2, C922.2, C923.2, C924.2, C925.2, C926.2, C927.2, C928.2, C929.2, C930.2, C931.2, C932.2, C933.2, C934.2, C951.2, C952.2, C953.2, C954.2, C955.2, C956.2, C957.2, C958.2, C959.2, C960.2, C965.2, C966.2, C967.2, C968.2, D1.2, D2.2, J1.A1, J1.A2, J1.A3, J1.A4, J1.A5, J1.A6, J1.A13, J1.A16, J1.A19, J1.A22, J1.A25, J1.A28, J1.B13, J1.B16, J1.B19, J1.B22, J1.B25, J1.B28, J2.A1, J2.A2, J2.A3, J2.A4, J2.A5, J2.A6, J2.A13, J2.A16, J2.A19, J2.A22, J2.A25, J2.A28, J2.B13, J2.B16, J2.B19, J2.B22, J2.B25, J2.B28, J3.A1, J3.A2, J3.A3, J3.A4, J3.A5, J3.A6, J3.A13, J3.A16, J3.A19, J3.A22, J3.A25, J3.A28, J3.B13, J3.B16, J3.B19, J3.B22, J3.B25, J3.B28, J4.A1, J4.A2, J4.A3, J4.A4, J4.A5, J4.A6, J4.A13, J4.A16, J4.A19, J4.A22, J4.A25, J4.A28, J4.B13, J4.B16, J4.B19, J4.B22, J4.B25, J4.B28, J5.A1, J5.A2, J5.A3, J5.A4, J5.A5, J5.A6, J5.A13, J5.A16, J5.A19, J5.A22, J5.A25, J5.A28, J5.B13, J5.B16, J5.B19, J5.B22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
/P3V3_AUX: C314.1, C315.1, C707.1, C720.1, C721.1, C722.1, C723.1, C724.1, C725.1, C726.1, C727.1, C730.1, C731.1, C732.1, C733.1, C734.1, C735.1, C736.1, C737.1, C742.1, J1.B11, J2.B11, J3.B11, J4.B11, J5.B11, J6.B11, J7.B11, J8.B11, J9.B11, J10.B11, L31.2, R311.1, R721.1, R722.1, U1.W32, U31.14, U601.1, U601.3, U601.10, U601.15, U601.19, U601.27, U601.34, U601.38, U601.42, U601.47, U601.48, U602.1, U602.3, U602.10, U602.15, U602.19, U602.27, U602.34, U602.38, U602.42, U602.47, U602.48, U605.6, U607.21, U702.1, U702.3
/P12_SLOT01: C103.1, J1.B1, J1.B2, J1.B3, J1.B4, J1.B5, J1.B6, U11.6
/P12_SLOT02: C106.1, J2.B1, J2.B2, J2.B3, J2.B4, J2.B5, J2.B6, U12.6
/P12_SLOT03: C109.1, J3.B1, J3.B2, J3.B3, J3.B4, J3.B5, J3.B6, U13.6
/P12_SLOT04: C112.1, J4.B1, J4.B2, J4.B3, J4.B4, J4.B5, J4.B6, U14.6
/P12_SLOT05: C115.1, J5.B1, J5.B2, J5.B3, J5.B4, J5.B5, J5.B6, U15.6
/P12_SLOT06: C118.1, J6.B1, J6.B2, J6.B3, J6.B4, J6.B5, J6.B6, U16.6
/P12_SLOT07: C121.1, J7.B1, J7.B2, J7.B3, J7.B4, J7.B5, J7.B6, U17.6
/P12_SLOT08: C124.1, J8.B1, J8.B2, J8.B3, J8.B4, J8.B5, J8.B6, U18.6
/P12_SLOT09: C127.1, J9.B1, J9.B2, J9.B3, J9.B4, J9.B5, J9.B6, U19.6
/P12_SLOT10: C130.1, J10.B1, J10.B2, J10.B3, J10.B4, J10.B5, J10.B6, U20.6
/PEX_0V9: U1.AA2, U1.AA4, U1.AA6, U1.AA8, U1.AA10, U1.AA12, U1.AB7, U1.AB13, U1.AB25, U1.AB31, U1.AC2, U1.AC20, U1.AC22, U1.AC24, U1.AC26, U1.AC28, U1.AC30, U1.AE2, U1.AE4, U1.AE6, U1.AE8, U1.AE10, U1.AE22, U1.AE24, U1.AE26, U1.AE28, U1.AE30, U1.AF1, U1.AG2, U1.AG4, U1.AG6, U1.AG8, U1.AG10, U1.AG24, U1.AG26, U1.AG28, U1.AG30, U1.AH1, U1.AH7, U1.U6, U1.U8, U1.U10, U1.U24, U1.U26, U1.V25, U1.V27, U1.V29, U1.V31, U1.W2, U1.W4, U1.W30, U1.Y1, U1.Y3, U1.Y5, U1.Y7, U1.Y9, U605.5
/PEX_0V9A: U1.AE20, U1.AF31, U1.AG12, U1.AG22, U1.AH13, U1.AJ6, U1.AJ10, U1.AJ14, U1.AJ18, U1.AJ22, U1.AJ26, U1.AJ30, U1.AK9, U1.AK11, U1.AK13, U1.AK15, U1.AK17, U1.AK19, U1.AK29, U1.AL2, U1.AL6, U1.AL10, U1.AL14, U1.AL18, U1.AL22, U1.AL30, U1.AM5, U1.AM11, U1.AM17, U1.AM23, U1.AM29, U1.L10, U1.L14, U1.L22, U1.L28, U1.M1, U1.M23, U1.N2, U1.N6, U1.N10, U1.N26, U1.N30, U1.P1, U1.P5, U1.P11, U1.P23, U1.P25, U1.P27, U1.P29, U1.P31, U1.R6, U1.R10, U1.R28, U1.T1, U1.T5, U1.T9, U1.T25, U1.U4, U1.U28, U1.V23, U1.W6
/PEX_1V8: R724.2, U1.AA22, U1.AA24, U1.AC4, U1.AC6, U1.AD1, U1.AD7, U1.AD13, U1.AD19, U1.AE12, U1.AE14, U1.AE18, U1.AF7, U1.AF13, U1.AF25, U1.AG14, U1.AG20, U1.AH19, U1.AJ4, U1.AJ8, U1.AJ12, U1.AJ16, U1.AJ20, U1.AJ24, U1.AJ28, U1.AK1, U1.AK7, U1.AK21, U1.AK27, U1.AK31, U1.AL4, U1.AL8, U1.AL12, U1.AL16, U1.AL20, U1.AL24, U1.M31, U1.N4, U1.N8, U1.N22, U1.N28, U1.N32, U1.P3, U1.P7, U1.R4, U1.R8, U1.R26, U1.R30, U1.T3, U1.T7, U1.T23, U1.T27, U1.T29, U1.T31, U1.V1, U1.V3, U1.V5, U1.V7, U1.V9, U1.W8, U1.W10, U1.W24, U1.W26, U1.Y23, U1.Y25, U1.Y27, U606.8
/PEX_1V8A: U1.AA30, U1.AB1, U1.AC16, U1.AC18, U1.AD25, U1.AD31, U1.AE16, U1.AF19, U1.AG16, U1.AG18, U1.AH25, U1.AJ2, U1.AK3, U1.AK5, U1.AK23, U1.AK25, U1.AL26, U1.AL28, U1.AM1, U1.AM7, U1.AM13, U1.AM19, U1.AM25, U1.AM31, U1.L8, U1.L12, U1.L20, U1.L26, U1.L30, U1.M7, U1.M25, U1.P9, U1.R2, U1.U2, U1.U30, U1.W28, U1.Y11, U1.Y29, U1.Y31
/PEX_RESET_CT: C741.1, U605.4
/PEX_SPI_CLK: U1.AF32, U606.6
/PEX_SPI_CS_N: U1.AJ32, U606.1
/PEX_SPI_IO0: U1.AB32, U606.5
/PEX_SPI_IO1: U1.AH31, U606.2
/PEX_SPI_IO2: U1.AE32, U606.3
/PEX_SPI_IO3: U1.AK32, U606.7
/PEX_SYS_REFCLK_N: U1.B29, U601.14
/PEX_SYS_REFCLK_P: U1.A29, U601.13
/PEX_SYS_RESET_N: R724.1, U1.AL32, U605.1
/REF_KA_VDD: U603.3, U603.7, U603.11, U603.20
/S01_PERST0_N: J1.B10, U1.AM3
/S01_PWR_DVDT: C101.1, U11.7
/S01_PWR_ILM: R105.1, U11.9
/S01_PWR_OV: R103.2, R104.1, U11.2
/S01_PWR_UV: R101.2, R102.1, U11.1
/S01_REFCLK0_N: J1.B14, U601.17
/S01_REFCLK0_P: J1.B15, U601.16
/S01_SSD_RX0_N: C4002.2, J1.B17
/S01_SSD_RX0_P: C4001.2, J1.B18
/S01_SSD_RX1_N: C4004.2, J1.B20
/S01_SSD_RX1_P: C4003.2, J1.B21
/S01_SSD_RX2_N: C4006.2, J1.B23
/S01_SSD_RX2_P: C4005.2, J1.B24
/S01_SSD_RX3_N: C4008.2, J1.B26
/S01_SSD_RX3_P: C4007.2, J1.B27
/S01_SW_RX0_N: J1.A17, U1.M5
/S01_SW_RX0_P: J1.A18, U1.L5
/S01_SW_RX1_N: J1.A20, U1.K5
/S01_SW_RX1_P: J1.A21, U1.J5
/S01_SW_RX2_N: J1.A23, U1.H5
/S01_SW_RX2_P: J1.A24, U1.G5
/S01_SW_RX3_N: J1.A26, U1.F5
/S01_SW_RX3_P: J1.A27, U1.E5
/S01_SW_TX0_N: C4002.1, U1.M3
/S01_SW_TX0_P: C4001.1, U1.L3
/S01_SW_TX1_N: C4004.1, U1.K3
/S01_SW_TX1_P: C4003.1, U1.J3
/S01_SW_TX2_N: C4006.1, U1.H3
/S01_SW_TX2_P: C4005.1, U1.G3
/S01_SW_TX3_N: C4008.1, U1.F3
/S01_SW_TX3_P: C4007.1, U1.E3
/S02_PERST0_N: J2.B10, U1.AM6
/S02_PWR_DVDT: C104.1, U12.7
/S02_PWR_ILM: R110.1, U12.9
/S02_PWR_OV: R108.2, R109.1, U12.2
/S02_PWR_UV: R106.2, R107.1, U12.1
/S02_REFCLK0_N: J2.B14, U601.22
/S02_REFCLK0_P: J2.B15, U601.21
/S02_SSD_RX0_N: C4010.2, J2.B17
/S02_SSD_RX0_P: C4009.2, J2.B18
/S02_SSD_RX1_N: C4012.2, J2.B20
/S02_SSD_RX1_P: C4011.2, J2.B21
/S02_SSD_RX2_N: C4014.2, J2.B23
/S02_SSD_RX2_P: C4013.2, J2.B24
/S02_SSD_RX3_N: C4016.2, J2.B26
/S02_SSD_RX3_P: C4015.2, J2.B27
/S02_SW_RX0_N: J2.A17, U1.M11
/S02_SW_RX0_P: J2.A18, U1.L11
/S02_SW_RX1_N: J2.A20, U1.K11
/S02_SW_RX1_P: J2.A21, U1.J11
/S02_SW_RX2_N: J2.A23, U1.H11
/S02_SW_RX2_P: J2.A24, U1.G11
/S02_SW_RX3_N: J2.A26, U1.F11
/S02_SW_RX3_P: J2.A27, U1.E11
/S02_SW_TX0_N: C4010.1, U1.M9
/S02_SW_TX0_P: C4009.1, U1.L9
/S02_SW_TX1_N: C4012.1, U1.K9
/S02_SW_TX1_P: C4011.1, U1.J9
/S02_SW_TX2_N: C4014.1, U1.H9
/S02_SW_TX2_P: C4013.1, U1.G9
/S02_SW_TX3_N: C4016.1, U1.F9
/S02_SW_TX3_P: C4015.1, U1.E9
/S03_PERST0_N: J3.B10, U1.AM9
/S03_PWR_DVDT: C107.1, U13.7
/S03_PWR_ILM: R115.1, U13.9
/S03_PWR_OV: R113.2, R114.1, U13.2
/S03_PWR_UV: R111.2, R112.1, U13.1
/S03_REFCLK0_N: J3.B14, U601.26
/S03_REFCLK0_P: J3.B15, U601.25
/S03_SSD_RX0_N: C4018.2, J3.B17
/S03_SSD_RX0_P: C4017.2, J3.B18
/S03_SSD_RX1_N: C4020.2, J3.B20
/S03_SSD_RX1_P: C4019.2, J3.B21
/S03_SSD_RX2_N: C4022.2, J3.B23
/S03_SSD_RX2_P: C4021.2, J3.B24
/S03_SSD_RX3_N: C4024.2, J3.B26
/S03_SSD_RX3_P: C4023.2, J3.B27
/S03_SW_RX0_N: J3.A17, U1.M17
/S03_SW_RX0_P: J3.A18, U1.L17
/S03_SW_RX1_N: J3.A20, U1.K17
/S03_SW_RX1_P: J3.A21, U1.J17
/S03_SW_RX2_N: J3.A23, U1.H17
/S03_SW_RX2_P: J3.A24, U1.G17
/S03_SW_RX3_N: J3.A26, U1.F17
/S03_SW_RX3_P: J3.A27, U1.E17
/S03_SW_TX0_N: C4018.1, U1.M15
/S03_SW_TX0_P: C4017.1, U1.L15
/S03_SW_TX1_N: C4020.1, U1.K15
/S03_SW_TX1_P: C4019.1, U1.J15
/S03_SW_TX2_N: C4022.1, U1.H15
/S03_SW_TX2_P: C4021.1, U1.G15
/S03_SW_TX3_N: C4024.1, U1.F15
/S03_SW_TX3_P: C4023.1, U1.E15
/S04_PERST0_N: J4.B10, U1.AM12
/S04_PWR_DVDT: C110.1, U14.7
/S04_PWR_ILM: R120.1, U14.9
/S04_PWR_OV: R118.2, R119.1, U14.2
/S04_PWR_UV: R116.2, R117.1, U14.1
/S04_REFCLK0_N: J4.B14, U601.29
/S04_REFCLK0_P: J4.B15, U601.28
/S04_SSD_RX0_N: C4026.2, J4.B17
/S04_SSD_RX0_P: C4025.2, J4.B18
/S04_SSD_RX1_N: C4028.2, J4.B20
/S04_SSD_RX1_P: C4027.2, J4.B21
/S04_SSD_RX2_N: C4030.2, J4.B23
/S04_SSD_RX2_P: C4029.2, J4.B24
/S04_SSD_RX3_N: C4032.2, J4.B26
/S04_SSD_RX3_P: C4031.2, J4.B27
/S04_SW_RX0_N: J4.A17, U1.T24
/S04_SW_RX0_P: J4.A18, U1.R24
/S04_SW_RX1_N: J4.A20, U1.P24
/S04_SW_RX1_P: J4.A21, U1.N24
/S04_SW_RX2_N: J4.A23, U1.M24
/S04_SW_RX2_P: J4.A24, U1.L24
/S04_SW_RX3_N: J4.A26, U1.K24
/S04_SW_RX3_P: J4.A27, U1.J24
/S04_SW_TX0_N: C4026.1, U1.M21
/S04_SW_TX0_P: C4025.1, U1.L21
/S04_SW_TX1_N: C4028.1, U1.K21
/S04_SW_TX1_P: C4027.1, U1.J21
/S04_SW_TX2_N: C4030.1, U1.H21
/S04_SW_TX2_P: C4029.1, U1.G21
/S04_SW_TX3_N: C4032.1, U1.F21
/S04_SW_TX3_P: C4031.1, U1.E21
/S05_PERST0_N: J5.B10, U1.AM15
/S05_PWR_DVDT: C113.1, U15.7
/S05_PWR_ILM: R125.1, U15.9
/S05_PWR_OV: R123.2, R124.1, U15.2
/S05_PWR_UV: R121.2, R122.1, U15.1
/S05_REFCLK0_N: J5.B14, U601.33
/S05_REFCLK0_P: J5.B15, U601.32
/S05_SSD_RX0_N: C4034.2, J5.B17
/S05_SSD_RX0_P: C4033.2, J5.B18
/S05_SSD_RX1_N: C4036.2, J5.B20
/S05_SSD_RX1_P: C4035.2, J5.B21
/S05_SSD_RX2_N: C4038.2, J5.B23
/S05_SSD_RX2_P: C4037.2, J5.B24
/S05_SSD_RX3_N: C4040.2, J5.B26
/S05_SSD_RX3_P: C4039.2, J5.B27
/S05_SW_RX0_N: J5.A17, U1.M29
/S05_SW_RX0_P: J5.A18, U1.L29
/S05_SW_RX1_N: J5.A20, U1.K29
/S05_SW_RX1_P: J5.A21, U1.J29
/S05_SW_RX2_N: J5.A23, U1.H29
/S05_SW_RX2_P: J5.A24, U1.G29
/S05_SW_RX3_N: J5.A26, U1.F29
/S05_SW_RX3_P: J5.A27, U1.E29
/S05_SW_TX0_N: C4034.1, U1.M27
/S05_SW_TX0_P: C4033.1, U1.L27
/S05_SW_TX1_N: C4036.1, U1.K27
/S05_SW_TX1_P: C4035.1, U1.J27
/S05_SW_TX2_N: C4038.1, U1.H27
/S05_SW_TX2_P: C4037.1, U1.G27
/S05_SW_TX3_N: C4040.1, U1.F27
/S05_SW_TX3_P: C4039.1, U1.E27
/S06_PERST0_N: J6.B10, U1.AM18
/S06_PWR_DVDT: C116.1, U16.7
/S06_PWR_ILM: R130.1, U16.9
/S06_PWR_OV: R128.2, R129.1, U16.2
/S06_PWR_UV: R126.2, R127.1, U16.1
/S06_REFCLK0_N: J6.B14, U601.36
/S06_REFCLK0_P: J6.B15, U601.35
/S06_SSD_RX0_N: C4042.2, J6.B17
/S06_SSD_RX0_P: C4041.2, J6.B18
/S06_SSD_RX1_N: C4044.2, J6.B20
/S06_SSD_RX1_P: C4043.2, J6.B21
/S06_SSD_RX2_N: C4046.2, J6.B23
/S06_SSD_RX2_P: C4045.2, J6.B24
/S06_SSD_RX3_N: C4048.2, J6.B26
/S06_SSD_RX3_P: C4047.2, J6.B27
/S06_SW_RX0_N: J6.A17, U1.AJ5
/S06_SW_RX0_P: J6.A18, U1.AH5
/S06_SW_RX1_N: J6.A20, U1.AG5
/S06_SW_RX1_P: J6.A21, U1.AF5
/S06_SW_RX2_N: J6.A23, U1.AE5
/S06_SW_RX2_P: J6.A24, U1.AD5
/S06_SW_RX3_N: J6.A26, U1.AC5
/S06_SW_RX3_P: J6.A27, U1.AB5
/S06_SW_TX0_N: C4042.1, U1.AJ3
/S06_SW_TX0_P: C4041.1, U1.AH3
/S06_SW_TX1_N: C4044.1, U1.AG3
/S06_SW_TX1_P: C4043.1, U1.AF3
/S06_SW_TX2_N: C4046.1, U1.AE3
/S06_SW_TX2_P: C4045.1, U1.AD3
/S06_SW_TX3_N: C4048.1, U1.AC3
/S06_SW_TX3_P: C4047.1, U1.AB3
/S07_PERST0_N: J7.B10, U1.AM21
/S07_PWR_DVDT: C119.1, U17.7
/S07_PWR_ILM: R135.1, U17.9
/S07_PWR_OV: R133.2, R134.1, U17.2
/S07_PWR_UV: R131.2, R132.1, U17.1
/S07_REFCLK0_N: J7.B14, U601.40
/S07_REFCLK0_P: J7.B15, U601.39
/S07_SSD_RX0_N: C4050.2, J7.B17
/S07_SSD_RX0_P: C4049.2, J7.B18
/S07_SSD_RX1_N: C4052.2, J7.B20
/S07_SSD_RX1_P: C4051.2, J7.B21
/S07_SSD_RX2_N: C4054.2, J7.B23
/S07_SSD_RX2_P: C4053.2, J7.B24
/S07_SSD_RX3_N: C4056.2, J7.B26
/S07_SSD_RX3_P: C4055.2, J7.B27
/S07_SW_RX0_N: J7.A17, U1.AJ11
/S07_SW_RX0_P: J7.A18, U1.AH11
/S07_SW_RX1_N: J7.A20, U1.AG11
/S07_SW_RX1_P: J7.A21, U1.AF11
/S07_SW_RX2_N: J7.A23, U1.AE11
/S07_SW_RX2_P: J7.A24, U1.AD11
/S07_SW_RX3_N: J7.A26, U1.AC11
/S07_SW_RX3_P: J7.A27, U1.AB11
/S07_SW_TX0_N: C4050.1, U1.AJ9
/S07_SW_TX0_P: C4049.1, U1.AH9
/S07_SW_TX1_N: C4052.1, U1.AG9
/S07_SW_TX1_P: C4051.1, U1.AF9
/S07_SW_TX2_N: C4054.1, U1.AE9
/S07_SW_TX2_P: C4053.1, U1.AD9
/S07_SW_TX3_N: C4056.1, U1.AC9
/S07_SW_TX3_P: C4055.1, U1.AB9
/S08_PERST0_N: J8.B10, U1.AM24
/S08_PWR_DVDT: C122.1, U18.7
/S08_PWR_ILM: R140.1, U18.9
/S08_PWR_OV: R138.2, R139.1, U18.2
/S08_PWR_UV: R136.2, R137.1, U18.1
/S08_REFCLK0_N: J8.B14, U602.14
/S08_REFCLK0_P: J8.B15, U602.13
/S08_SSD_RX0_N: C4058.2, J8.B17
/S08_SSD_RX0_P: C4057.2, J8.B18
/S08_SSD_RX1_N: C4060.2, J8.B20
/S08_SSD_RX1_P: C4059.2, J8.B21
/S08_SSD_RX2_N: C4062.2, J8.B23
/S08_SSD_RX2_P: C4061.2, J8.B24
/S08_SSD_RX3_N: C4064.2, J8.B26
/S08_SSD_RX3_P: C4063.2, J8.B27
/S08_SW_RX0_N: J8.A17, U1.AJ17
/S08_SW_RX0_P: J8.A18, U1.AH17
/S08_SW_RX1_N: J8.A20, U1.AG17
/S08_SW_RX1_P: J8.A21, U1.AF17
/S08_SW_RX2_N: J8.A23, U1.AE17
/S08_SW_RX2_P: J8.A24, U1.AD17
/S08_SW_RX3_N: J8.A26, U1.AC17
/S08_SW_RX3_P: J8.A27, U1.AB17
/S08_SW_TX0_N: C4058.1, U1.AJ15
/S08_SW_TX0_P: C4057.1, U1.AH15
/S08_SW_TX1_N: C4060.1, U1.AG15
/S08_SW_TX1_P: C4059.1, U1.AF15
/S08_SW_TX2_N: C4062.1, U1.AE15
/S08_SW_TX2_P: C4061.1, U1.AD15
/S08_SW_TX3_N: C4064.1, U1.AC15
/S08_SW_TX3_P: C4063.1, U1.AB15
/S09_PERST0_N: J9.B10, U1.AM27
/S09_PWR_DVDT: C125.1, U19.7
/S09_PWR_ILM: R145.1, U19.9
/S09_PWR_OV: R143.2, R144.1, U19.2
/S09_PWR_UV: R141.2, R142.1, U19.1
/S09_REFCLK0_N: J9.B14, U602.17
/S09_REFCLK0_P: J9.B15, U602.16
/S09_SSD_RX0_N: C4066.2, J9.B17
/S09_SSD_RX0_P: C4065.2, J9.B18
/S09_SSD_RX1_N: C4068.2, J9.B20
/S09_SSD_RX1_P: C4067.2, J9.B21
/S09_SSD_RX2_N: C4070.2, J9.B23
/S09_SSD_RX2_P: C4069.2, J9.B24
/S09_SSD_RX3_N: C4072.2, J9.B26
/S09_SSD_RX3_P: C4071.2, J9.B27
/S09_SW_RX0_N: J9.A17, U1.AJ23
/S09_SW_RX0_P: J9.A18, U1.AH23
/S09_SW_RX1_N: J9.A20, U1.AG23
/S09_SW_RX1_P: J9.A21, U1.AF23
/S09_SW_RX2_N: J9.A23, U1.AE23
/S09_SW_RX2_P: J9.A24, U1.AD23
/S09_SW_RX3_N: J9.A26, U1.AC23
/S09_SW_RX3_P: J9.A27, U1.AB23
/S09_SW_TX0_N: C4066.1, U1.AJ21
/S09_SW_TX0_P: C4065.1, U1.AH21
/S09_SW_TX1_N: C4068.1, U1.AG21
/S09_SW_TX1_P: C4067.1, U1.AF21
/S09_SW_TX2_N: C4070.1, U1.AE21
/S09_SW_TX2_P: C4069.1, U1.AD21
/S09_SW_TX3_N: C4072.1, U1.AC21
/S09_SW_TX3_P: C4071.1, U1.AB21
/S10_PERST0_N: J10.B10, U1.AM30
/S10_PWR_DVDT: C128.1, U20.7
/S10_PWR_ILM: R150.1, U20.9
/S10_PWR_OV: R148.2, R149.1, U20.2
/S10_PWR_UV: R146.2, R147.1, U20.1
/S10_REFCLK0_N: J10.B14, U602.22
/S10_REFCLK0_P: J10.B15, U602.21
/S10_SSD_RX0_N: C4074.2, J10.B17
/S10_SSD_RX0_P: C4073.2, J10.B18
/S10_SSD_RX1_N: C4076.2, J10.B20
/S10_SSD_RX1_P: C4075.2, J10.B21
/S10_SSD_RX2_N: C4078.2, J10.B23
/S10_SSD_RX2_P: C4077.2, J10.B24
/S10_SSD_RX3_N: C4080.2, J10.B26
/S10_SSD_RX3_P: C4079.2, J10.B27
/S10_SW_RX0_N: J10.A17, U1.AJ29
/S10_SW_RX0_P: J10.A18, U1.AH29
/S10_SW_RX1_N: J10.A20, U1.AG29
/S10_SW_RX1_P: J10.A21, U1.AF29
/S10_SW_RX2_N: J10.A23, U1.AE29
/S10_SW_RX2_P: J10.A24, U1.AD29
/S10_SW_RX3_N: J10.A26, U1.AC29
/S10_SW_RX3_P: J10.A27, U1.AB29
/S10_SW_TX0_N: C4074.1, U1.AJ27
/S10_SW_TX0_P: C4073.1, U1.AH27
/S10_SW_TX1_N: C4076.1, U1.AG27
/S10_SW_TX1_P: C4075.1, U1.AF27
/S10_SW_TX2_N: C4078.1, U1.AE27
/S10_SW_TX2_P: C4077.1, U1.AD27
/S10_SW_TX3_N: C4080.1, U1.AC27
/S10_SW_TX3_P: C4079.1, U1.AB27
/TB5_USB2_DN: J402.A7, J402.B7
/TB5_USB2_DP: J402.A6, J402.B6
/TB5_VBUS: J402.A4, J402.A9, J402.B4, J402.B9
/VBANK_A: C1.1, C102.1, C105.1, C108.1, C111.1, C114.1, D1.1, F1.2, R101.1, R103.1, R106.1, R108.1, R111.1, R113.1, R116.1, R118.1, R121.1, R123.1, R301.1, R303.1, U11.5, U12.5, U13.5, U14.5, U15.5, U30.5
/VBANK_B: C2.1, C117.1, C120.1, C123.1, C126.1, C129.1, D2.1, F2.2, R126.1, R128.1, R131.1, R133.1, R136.1, R138.1, R141.1, R143.1, R146.1, R148.1, U16.5, U17.5, U18.5, U19.5, U20.5
/VIN_A: F1.1, J11.1
/VIN_B: F2.1, J12.1
